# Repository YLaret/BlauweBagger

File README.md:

# BlauweBagger
This is the repository for the software that controls the Blauwe Bagger prototype installation.

## User Guide
After booting up the Raspberry Pi and going to the main page: [Main](http://192.168.0.100). The schematic overview should be visible (meters are being updated live, so can have different values):

The system always boots with all switches off (STOP mode).
### Automatic Control
To let the machine run on autopilot simply press `AUTO`. The machine will determine based on the sensors which pumps and motors to turn on/off.

### Manual Control
To control the switches manually, press `PAUSE` all the switches will turn off. Pressing on a pump or motor will turn it on/off. **Be careful: NO METER CONTROL, dangerous situation can occur.** 

### Timer Control (deprecated)
To run a timer based program, create stages with SwitchIDS and stageTimes and add these to a program. In the control view the program can be selected and executed. **NOTE:** the first program `Clay Unload` is a special program used by automatic control for the unload sequence, change with caution.

## Architecture
The controller is a Raspberry Pi module which controls the pumps and motors with Tuya enabled switches. The Pi will control the machine with a python service `machine.py`. This service will read the preferred state and write the actual state of the machine from and to a SQL database. A second service `server.py` hosts a local website that reads and writes the database values, allowing the user to control the machine remotely.
* `machine.py` will rely on the [gpiod](https://pypi.org/project/gpiod/) library for interaction with switches (GPIO)
* `server.py` will be based around Flask and nginx

### Database Architecture
The database follows a relational model with the following layout:

**NOTE1:** Upon upgrading the Tuya switches with SSR controlled by the GPIO, the **SWITCH** table does NOT contain: {MeterIDS, MeterMIN, MeterMax, IPAdress, LocalKey} anymore, instead: {SwitchID, Name, GPIO}.
**NOTE2:** A new table linking meters to switches called **METERRULES** containing:{MeterRuleID, MeterID, MeterThreshold, MeterThresholdGEQ, SwitchID, SwitchBool, Stage}.
## General Design Requirements
* ✅ Controlling pumps (manual, timed and automatic (senorbased)) using WebUI
* ✅ Flowmeter visualization in WebUI
* ✅ Pump control based on pressuresensor
* ✅ Log pump data (flow and power)
* ✅ Log and display errors and stalls
* ✅ Be transferable to new systems

### Webserver Design Requirements
* ✅ Schematic and tableview
* ✅ Way to create programs and controll machine manually
* ✅ Tableview with meters table, motors table and log window
* ✅ Schematicview with visualization of the plant (motor and flow meter states) and a log window
* ✅ Program view with timing possibilities

## Installation
### Installing Rasbian
* Download [Raspberry Pi OS Lite (64-bit)](https://www.raspberrypi.com/software/operating-systems/)
* Use Rasbian Imager to etch OS on an SD card
* Turn on SSH and add user `pi` with password [...]
* SSH into the Pi:
`ssh pi@[ipaddress]`
* Install pip, git and nginx:
```
sudo apt update
sudo apt upgrade
sudo apt install pip
sudo apt install git
sudo apt install nginx
```

Make sure python and pip are installed
* Clone the repository 
`git clone https://github.com/YLaret/BlauweBagger`
* Go to the BlauweBagger directory 
`cd BlauweBagger`
* Install the python dependencies 
`sudo pip install -r requirements.txt --break-system-packages`

## Running the webserver (for quick dev)
To run the webserver in developer modus:
```
cd server
export FLASK_APP=server
flask run --host=0.0.0.0
```
* After making some changes to the `server.py`, the server can be stopped by Ctr+C and restarted by the previous command

## Installing the webserver (permanent usage)
* Create a service for the server:
`sudo nano /etc/systemd/system/BlauweBagger.service`
* Copy paste the following:

```
[Unit]
Description=uWSGI instance to serve BlauweBagger server
After=network.target

[Service]
User=pi
Group=www-data
WorkingDirectory=/home/pi/BlauweBagger/server
ExecStart=/usr/local/bin/uwsgi --ini server.ini

[Install]
WantedBy=multi-user.target
```
* Enable the service:
```
sudo systemctl start BlauweBagger
sudo systemctl enable BlauweBagger
```

* Create start up script to fix permissions:
`sudo nano /etc/systemd/system/FixSocketPermissions.service`
* Copy and past the following:
```
[Unit]
Description=Fix socket permissions
After=network.target BlauweBagger.service

[Service]
ExecStart=/bin/bash -c "sudo chown pi:www-data /home/pi/BlauweBagger/server/server.sock; sudo chmod 660 /home/pi/BlauweBagger/server/server.sock; sudo chmod 755 /home/pi"
Type=oneshot
RemainAfterExit=yes

[Install]
WantedBy=multi-user.target
```
* Activate script:
```
sudo systemctl daemon-reload
sudo systemctl enable FixSocketPermissions
sudo systemctl start FixSocketPermissions
```

* Configure Nginx to proxy Request:
`sudo nano /etc/nginx/sites-available/BlauweBagger`
* Copy paste the following:

```
server {
    listen 80;
    server_name _;
location / {
        include uwsgi_params;
        uwsgi_pass unix:/home/pi/BlauweBagger/server/server.sock;
    }
}
```
* Link to enabled sites:
`sudo ln -s /etc/nginx/sites-available/BlauweBagger /etc/nginx/sites-enabled`
* Restart Nginx:
`sudo systemctl restart nginx`

## Running the machine program (for quick dev)
To run the machine program in developer modus:
```
cd machine
python machine.py
```

Exit the program with Ctr+C

## Installing the machine program (permanent usage)
* Create the service `sudo nano /etc/systemd/system/BlauweBaggerMachine.service`
* Copy and past the following:
```
[Unit]
Description=Python script controlling the machine
After=network.target

[Service]
User=pi
WorkingDirectory=/home/pi/BlauweBagger/machine
ExecStart=/usr/bin/python /home/pi/BlauweBagger/machine/machine.py
Restart=on-abort

[Install]
WantedBy=multi-user.target
```
* Start the script
```
sudo systemctl daemon-reload
sudo systemctl start BlauweBaggerMachine
sudo systemctl enable BlauweBaggerMachine
```

## Running the control program (for quick dev)
To run the control program in developer modus:
```
cd control
python control.py
```

Exit the program with Ctr+C

## Installing the machine program (permanent usage)
* Create the service `sudo nano /etc/systemd/system/BlauweBaggerControl.service`
* Copy and past the following:
```
[Unit]
Description=Python script controlling the hydrocyclone
After=network.target

[Service]
User=pi
WorkingDirectory=/home/pi/BlauweBagger/control
ExecStart=/usr/bin/python /home/pi/BlauweBagger/control/control.py
Restart=on-abort

[Install]
WantedBy=multi-user.target
```
* Start the script
```
sudo systemctl daemon-reload
sudo systemctl start BlauweBaggerControl
sudo systemctl enable BlauweBaggerControl
```
## Hydrocyclone Control
The ACC page provides hydrocyclone control. The `Ref` entry of the `CONTROL` table in the `machine.db` Sqlite3 database is used to determine the set point, the `auto` entry is used to toggle sensor control (e.g. when a sensor fails possible to turn of automatic control of the VFD). The control service source code is `control/control.py`.

## Tailscale (remote access)
To access the installation remotely Tailscale is used to create a mesh VPN to which the Raspberry Pi and the control client are connected. To install follow the [instructions](https://pypi.org/project/gpiod/) to install on the Raspberry Pi, login with an account (e.g. `blueboxvpn@gmail.com`) and install on the control client side as well (iOS, macOS, Windows or Linux) and login with the same account. Go to the ip-address of the Raspberry Pi (visible on Tailscale dashboard). On the control client connect to the Tailscale VPN and

## 5G router setup (Zyxel NR5307)
Check the connected devices and note the MAC-address of the raspberrypi (e.g. 1c:cf:67:67:3c:d8). Go to Home Network->Static DHCP insert a configuration with the MAC-address and the preferred IP-address (e.g. 192.168.1.100). This will be url to which local (non-VPN) devices (e.g. iPad) can connect to the machine.

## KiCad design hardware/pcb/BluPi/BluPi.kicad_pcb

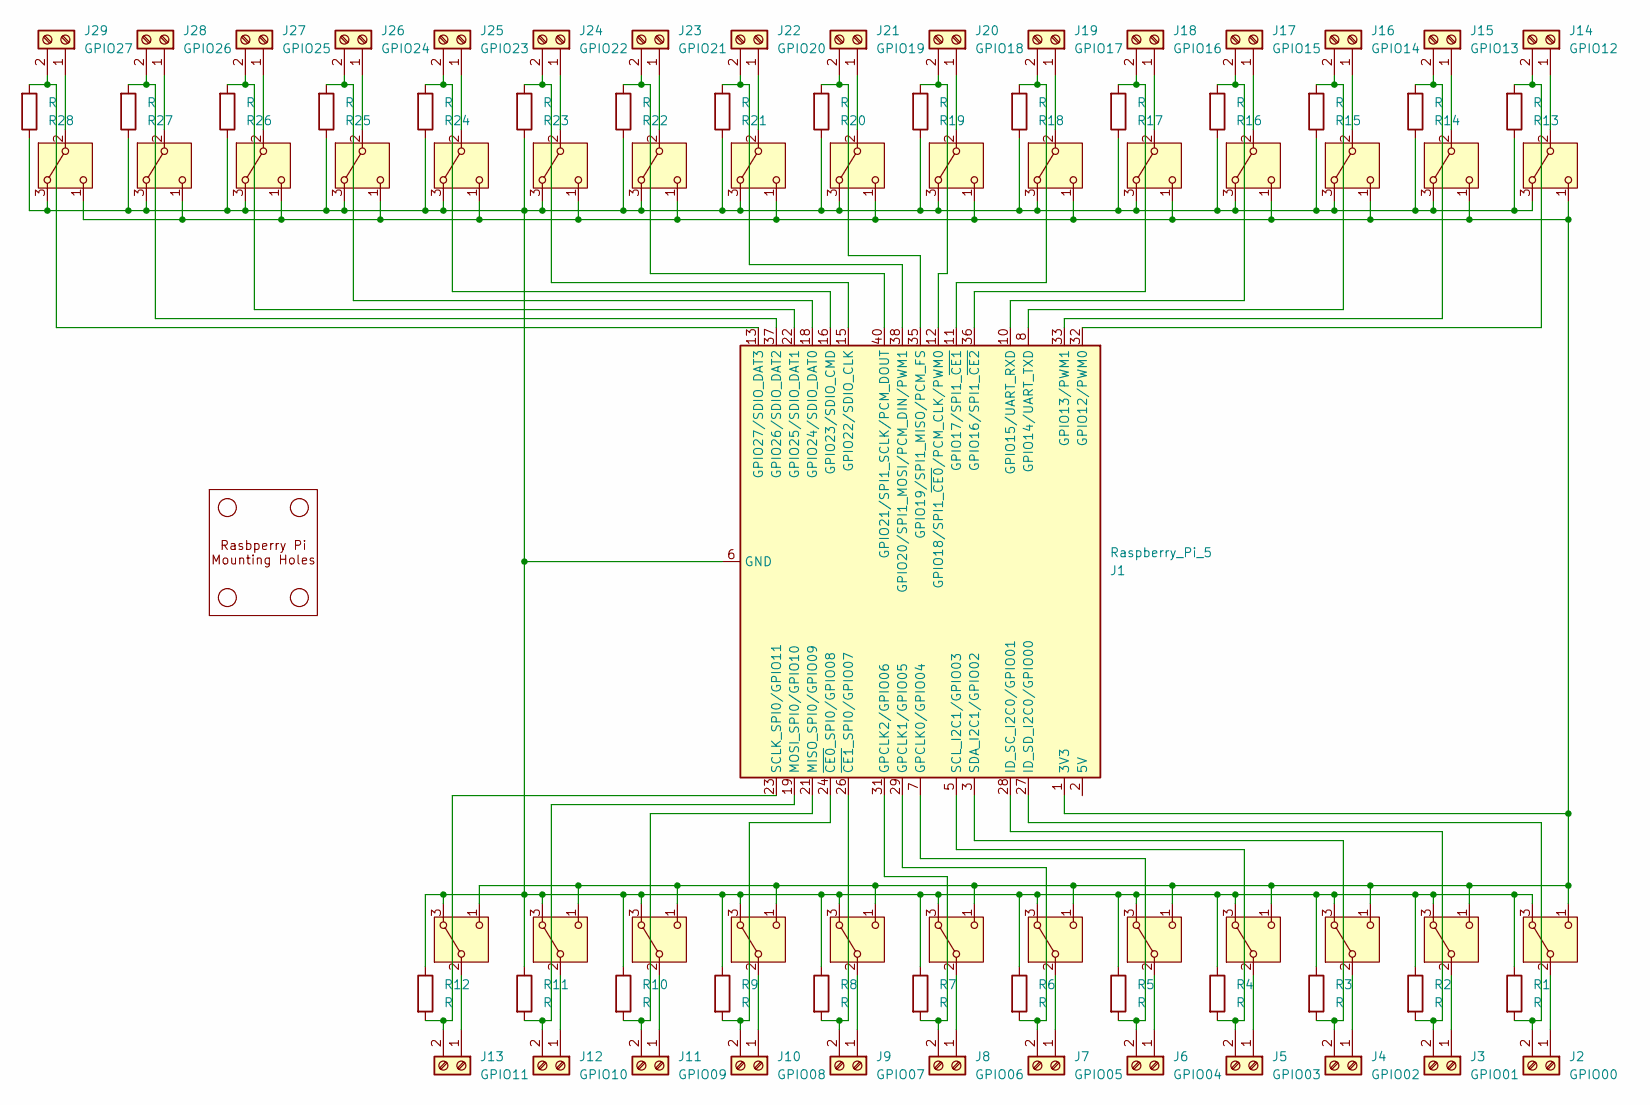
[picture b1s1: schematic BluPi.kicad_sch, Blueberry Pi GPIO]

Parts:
J1: Raspberry_Pi_5; PinHeader_2x20_P2.54mm_Vertical
J2: GPIO00; TerminalBlock_Phoenix_MKDS-1,5-2-5.08_1x02_P5.08mm_Horizont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
J3: GPIO01; TerminalBlock_Phoenix_MKDS-1,5-2-5.08_1x02_P5.08mm_Horizont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
J4: GPIO02; TerminalBlock_Phoenix_MKDS-1,5-2-5.08_1x02_P5.08mm_Horizont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
J5: GPIO03; TerminalBlock_Phoenix_MKDS-1,5-2-5.08_1x02_P5.08mm_Horizont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
J6: GPIO04; TerminalBlock_Phoenix_MKDS-1,5-2-5.08_1x02_P5.08mm_Horizont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
J7: GPIO05; TerminalBlock_Phoenix_MKDS-1,5-2-5.08_1x02_P5.08mm_Horizont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
J8: GPIO06; TerminalBlock_Phoenix_MKDS-1,5-2-5.08_1x02_P5.08mm_Horizont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
J9: GPIO07; TerminalBlock_Phoenix_MKDS-1,5-2-5.08_1x02_P5.08mm_Horizont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
J10: GPIO08; TerminalBlock_Phoenix_MKDS-1,5-2-5.08_1x02_P5.08mm_Horizont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
J11: GPIO09; TerminalBlock_Phoenix_MKDS-1,5-2-5.08_1x02_P5.08mm_Horizont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
J12: GPIO10; TerminalBlock_Phoenix_MKDS-1,5-2-5.08_1x02_P5.08mm_Horizont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
J13: GPIO11; TerminalBlock_Phoenix_MKDS-1,5-2-5.08_1x02_P5.08mm_Horizont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
J14: GPIO12; TerminalBlock_Phoenix_MKDS-1,5-2-5.08_1x02_P5.08mm_Horizont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
J15: GPIO13; TerminalBlock_Phoenix_MKDS-1,5-2-5.08_1x02_P5.08mm_Horizont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
J16: GPIO14; TerminalBlock_Phoenix_MKDS-1,5-2-5.08_1x02_P5.08mm_Horizont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
J17: GPIO15; TerminalBlock_Phoenix_MKDS-1,5-2-5.08_1x02_P5.08mm_Horizont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
J18: GPIO16; TerminalBlock_Phoenix_MKDS-1,5-2-5.08_1x02_P5.08mm_Horizont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
J19: GPIO17; TerminalBlock_Phoenix_MKDS-1,5-2-5.08_1x02_P5.08mm_Horizont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
J20: GPIO18; TerminalBlock_Phoenix_MKDS-1,5-2-5.08_1x02_P5.08mm_Horizont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
J21: GPIO19; TerminalBlock_Phoenix_MKDS-1,5-2-5.08_1x02_P5.08mm_Horizont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
J22: GPIO20; TerminalBlock_Phoenix_MKDS-1,5-2-5.08_1x02_P5.08mm_Horizont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
J23: GPIO21; TerminalBlock_Phoenix_MKDS-1,5-2-5.08_1x02_P5.08mm_Horizont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
J24: GPIO22; TerminalBlock_Phoenix_MKDS-1,5-2-5.08_1x02_P5.08mm_Horizont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
J25: GPIO23; TerminalBlock_Phoenix_MKDS-1,5-2-5.08_1x02_P5.08mm_Horizont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
J26: GPIO24; TerminalBlock_Phoenix_MKDS-1,5-2-5.08_1x02_P5.08mm_Horizont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
J27: GPIO25; TerminalBlock_Phoenix_MKDS-1,5-2-5.08_1x02_P5.08mm_Horizont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
J28: GPIO26; TerminalBlock_Phoenix_MKDS-1,5-2-5.08_1x02_P5.08mm_Horizont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
J29: GPIO27; TerminalBlock_Phoenix_MKDS-1,5-2-5.08_1x02_P5.08mm_Horizont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
R1, R2, R3, R4, R5, R6, R7, R8, R9, R10, R11, R12, R13, R14, R15, R16, R17, R18, R19, R20, R21, R22, R23, R24, R25, R26, R27, R28: R; R_0201_0603Metric_Pad0.64x0.40mm_HandSolder
SW1, SW2, SW3, SW4, SW5, SW6, SW7, SW8, SW9, SW10, SW11, SW12, SW13, SW14, SW15, SW16, SW17, SW18, SW19, SW20, SW21, SW22, SW23, SW24, SW25, SW26, SW27, SW28: SW_Nidec_CAS-120A1; Nidec_Copal_CAS-120A
U1: (no value)

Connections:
unnamed: J1.2 (5V), J1.4 (5V)
unnamed: J1.7 (GPCLK0/GPIO04), J6.2, R5.2
unnamed: J1.29 (GPCLK1/GPIO05), J7.2, R6.2
unnamed: J1.31 (GPCLK2/GPIO06), J8.2, R7.2
unnamed: J1.32 (GPIO12/PWM0), J14.2, R13.2
unnamed: J1.33 (GPIO13/PWM1), J15.2, R14.2
unnamed: J1.8 (GPIO14/UART_TXD), J16.2, R15.2
unnamed: J1.10 (GPIO15/UART_RXD), J17.2, R16.2
unnamed: J1.36 (GPIO16/SPI1_~CE2), J18.2, R17.2
unnamed: J1.11 (GPIO17/SPI1_~CE1), J19.2, R18.2
unnamed: J1.12 (GPIO18/SPI1_~CE0/PCM_CLK/PWM0), J20.2, R19.2
unnamed: J1.35 (GPIO19/SPI1_MISO/PCM_FS), J21.2, R20.2
unnamed: J1.38 (GPIO20/SPI1_MOSI/PCM_DIN/PWM1), J22.2, R21.2
unnamed: J1.40 (GPIO21/SPI1_SCLK/PCM_DOUT), J23.2, R22.2
unnamed: J1.15 (GPIO22/SDIO_CLK), J24.2, R23.2
unnamed: J1.16 (GPIO23/SDIO_CMD), J25.2, R24.2
unnamed: J1.18 (GPIO24/SDIO_DAT0), J26.2, R25.2
unnamed: J1.22 (GPIO25/SDIO_DAT1), J27.2, R26.2
unnamed: J1.37 (GPIO26/SDIO_DAT2), J28.2, R27.2
unnamed: J1.13 (GPIO27/SDIO_DAT3), J29.2, R28.2
unnamed: J1.28 (ID_SC_I2C0/GPIO01), J3.2, R2.2
unnamed: J1.27 (ID_SD_I2C0/GPIO00), J2.2, R1.2
unnamed: J1.21 (MISO_SPI0/GPIO09), J11.2, R10.2
unnamed: J1.19 (MOSI_SPI0/GPIO10), J12.2, R11.2
unnamed: J1.23 (SCLK_SPI0/GPIO11), J13.2, R12.2
unnamed: J1.5 (SCL_I2C1/GPIO03), J5.2, R4.2
unnamed: J1.3 (SDA_I2C1/GPIO02), J4.2, R3.2
unnamed: J1.24 (~CE0_SPI0/GPIO08), J10.2, R9.2
unnamed: J1.26 (~CE1_SPI0/GPIO07), J9.2, R8.2
unnamed: J2.1, SW1.2 (B)
unnamed: J3.1, SW2.2 (B)
unnamed: J4.1, SW3.2 (B)
unnamed: J5.1, SW4.2 (B)
unnamed: J6.1, SW5.2 (B)
unnamed: J7.1, SW6.2 (B)
unnamed: J8.1, SW7.2 (B)
unnamed: J9.1, SW8.2 (B)
unnamed: J10.1, SW9.2 (B)
unnamed: J11.1, SW10.2 (B)
unnamed: J12.1, SW11.2 (B)
unnamed: J13.1, SW12.2 (B)
unnamed: J14.1, SW13.2 (B)
unnamed: J15.1, SW14.2 (B)
unnamed: J16.1, SW15.2 (B)
unnamed: J17.1, SW16.2 (B)
unnamed: J18.1, SW17.2 (B)
unnamed: J19.1, SW18.2 (B)
unnamed: J20.1, SW19.2 (B)
unnamed: J21.1, SW20.2 (B)
unnamed: J22.1, SW21.2 (B)
unnamed: J23.1, SW22.2 (B)
unnamed: J24.1, SW23.2 (B)
unnamed: J25.1, SW24.2 (B)
unnamed: J26.1, SW25.2 (B)
unnamed: J27.1, SW26.2 (B)
unnamed: J28.1, SW27.2 (B)
unnamed: J29.1, SW28.2 (B)
unnamed: J1.6 (GND), J1.9 (GND), J1.14 (GND), J1.20 (GND), J1.25 (GND), J1.30 (GND), J1.34 (GND), J1.39 (GND), R1.1, R2.1, R3.1, R4.1, R5.1, R6.1, R7.1, R8.1, R9.1, R10.1, R11.1, R12.1, R13.1, R14.1, R15.1, R16.1, R17.1, R18.1, R19.1, R20.1, R21.1, R22.1, R23.1, R24.1, R25.1, R26.1, R27.1, R28.1, SW1.3 (A), SW2.3 (A), SW3.3 (A), SW4.3 (A), SW5.3 (A), SW6.3 (A), SW7.3 (A), SW8.3 (A), SW9.3 (A), SW10.3 (A), SW11.3 (A), SW12.3 (A), SW13.3 (A), SW14.3 (A), SW15.3 (A), SW16.3 (A), SW17.3 (A), SW18.3 (A), SW19.3 (A), SW20.3 (A), SW21.3 (A), SW22.3 (A), SW23.3 (A), SW24.3 (A), SW25.3 (A), SW26.3 (A), SW27.3 (A), SW28.3 (A)
unnamed: J1.1 (3V3), J1.17 (3V3), SW1.1 (C), SW2.1 (C), SW3.1 (C), SW4.1 (C), SW5.1 (C), SW6.1 (C), SW7.1 (C), SW8.1 (C), SW9.1 (C), SW10.1 (C), SW11.1 (C), SW12.1 (C), SW13.1 (C), SW14.1 (C), SW15.1 (C), SW16.1 (C), SW17.1 (C), SW18.1 (C), SW19.1 (C), SW20.1 (C), SW21.1 (C), SW22.1 (C), SW23.1 (C), SW24.1 (C), SW25.1 (C), SW26.1 (C), SW27.1 (C), SW28.1 (C)

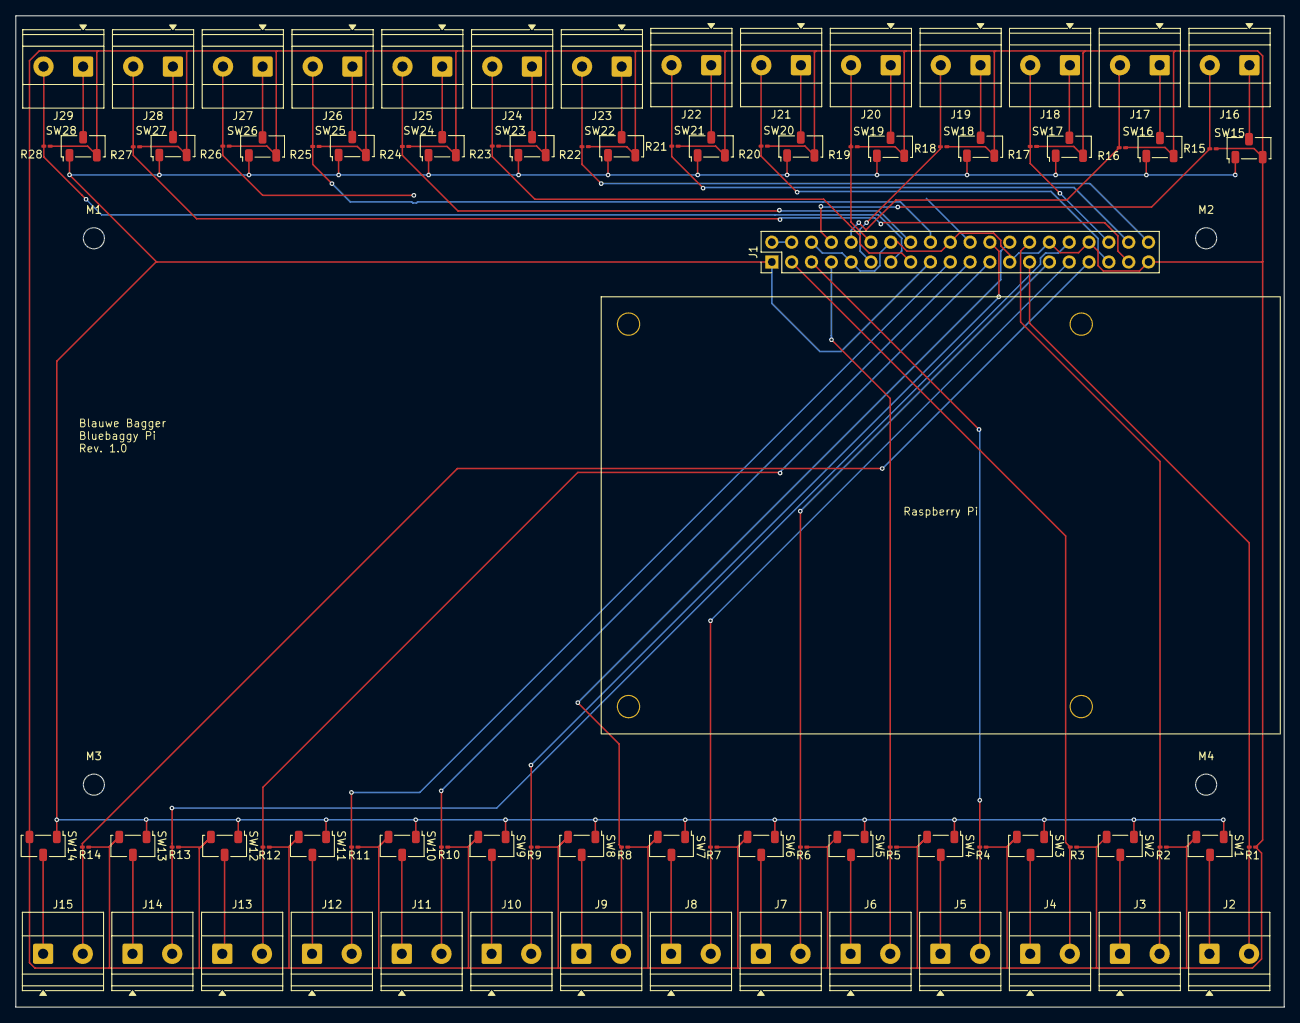
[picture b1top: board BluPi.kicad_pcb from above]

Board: 2 copper layers, 162.5 x 127.0 mm, 90 parts (0 on the bottom side), 59 nets.

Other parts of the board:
M1, M2, M3, M4: MountingHole_2.7mm
Raspberry Pi: Raspberry Pi 5 Mounting Holes; Raspberry_Pi_5_mounting_holes

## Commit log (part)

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2024-11-27 second commit
2024-11-27 third commit
2024-11-27 4 commit
2024-11-27 skirt
2024-11-27 wadabra
2024-11-27 clean sheet
2024-11-27 First sketch of the project
2024-11-27 small formatting fix
2024-12-02 added design requirements
2024-12-02 added transferability requirement
2024-12-02 added the main server start
2024-12-02 added requirements for webserver
2024-12-02 added an explantion of the database as well as the database architecture
2024-12-02 added the webserver developer running instructions
2024-12-02 added the machine outline
2024-12-02 added a first installation manual
2024-12-02 spelling fix
2024-12-02 added link to tinytuya
2024-12-02 updated the server instructions
2024-12-02 added sqlite3
2024-12-02 just a change of inventory
2024-12-02 first webserver outline framework
2024-12-02 inventory check
2024-12-02 first draft of webserver requirements
2024-12-02 formattting fix
2024-12-02 expanded requirements
2024-12-02 removed useless print statement
2024-12-03 increased automatic table generation
2024-12-03 implemented way to update database via the browser
2024-12-03 making the other table also updateable
2024-12-03 updated the column name to id in all tables
2024-12-03 added the tables to the program page, needs fix
2024-12-04 increased datatype compatability
2024-12-04 added a program table
2024-12-04 a start with the machine logic and program
2024-12-05 tuya library
2024-12-05 syntax error
2024-12-05 programState table
2024-12-05 improved automatic table generation
2024-12-05 a crude version of the machine executing programs
2024-12-05 updated explanation with new tables
2024-12-05 instructions for running the machine program
2024-12-05 formatting fix
2024-12-06 updated the description with the current state of the database
2024-12-07 proper closure of database connections in functions that access
2024-12-07 close database location fix
2024-12-07 fixed the close position really now
2024-12-07 syntax errors
2024-12-08 database diagram
2024-12-08 corrected link
2024-12-08 converted diagram to jpg
2024-12-09 localkey and old architecture
2024-12-09 EM1 and EM2 with localkey
2024-12-09 enabled the switching commands
2024-12-09 removed EM1 from database (main switch)
2024-12-09 device id is cryptic not EM1
2024-12-09 functional switches
2024-12-09 print statement more solid
2024-12-09 last tuya secret and modbus
2025-03-10 database architecture update
2025-03-10 readme with new archi
2025-03-10 readme with new archi (typo fix)
2025-03-10 readme with new archi (typo fix 2)
2025-03-11 database update and machine update
2025-03-11 added possibility to add rows and changed method modify rows
2025-03-11 half way backup commit (XCode is becoming unstable...)
2025-03-11 another backup push
2025-03-12 added flowsensor reading
2025-03-12 machine updates database with meter readings
2025-03-12 early phase auto update page
2025-03-12 typo fix
2025-03-12 another typo
2025-03-12 add jsonify lib
2025-03-12 typo
2025-03-12 log update
2025-03-12 check
2025-03-12 first attempt dynamic runtime
2025-03-12 dynamic meters, switches and runtime
2025-03-12 working dynamic homepage
2025-03-12 meter fix #1
2025-03-12 meter fix #2
2025-03-12 meter fix #3
2025-03-12 meter fix #4
2025-03-12 meter fix #5
2025-03-12 meter fix #6
2025-03-12 meter fix #7
2025-03-12 meter fixed
2025-03-12 last commit before pi transit
2025-03-12 leave switch 0/1 on in shutdown
2025-03-12 updated connect switches
2025-03-12 connect switch update
2025-03-12 removed switch 0 (idk where this one is, but it slows down the loop
2025-03-12 hopefully fixed speed problem
2025-03-12 speed attempt #1
2025-03-12 speed attempt #2
2025-03-19 database does not include critical switches
2025-03-19 removed wifi from readme
2025-03-19 added how to ssh into the pi
2025-03-19 added one program
2025-03-19 nowait var is the new speed up
2025-03-19 changed timing
2025-03-19 updated readme for installing permanent server
2025-03-19 readme typo
2025-03-19 added uwsgi req
2025-03-19 ini files
2025-03-19 time library
2025-03-19 changed turn off tuya
2025-03-19 better dsp for tuya 3.4
2025-03-19 machine install instructions
2025-03-19 fix with the nginx permissions
2025-03-20 added iPad 2 for dynamically updated webpages
2025-03-26 add a separate interval for the switches, async from the normal loop
2025-03-26 clarify the machine part of the read me
2025-03-30 more data on overview page
2025-03-30 forgot to return result
2025-03-30 now ther should be result
2025-03-31 resolved problem if no value
2025-03-31 first stage of overview remodelling
2025-03-31 java typo
2025-03-31 another java typo
2025-03-31 fixed stage out of bounds
2025-03-31 python syntax fix
2025-03-31 python logic fix
2025-03-31 indexing fix
2025-03-31 meter container and dynamic updates
2025-03-31 meter styling
2025-03-31 overview html architecture update
2025-03-31 forgotten class
2025-03-31 another forgotten class
2025-03-31 program info style update
2025-03-31 overview control architecture change
2025-03-31 final styling of overview
2025-03-31 active switch class fix
2025-03-31 ipad 2 button fix attempt #1
2025-03-31 ipad 2 button fix attempt #2
2025-03-31 some more old ipad fixes
2025-03-31 some more old ipad fixes #2
2025-03-31 last styling details
2025-03-31 last styling details for ipad 2
2025-03-31 limited the decimals on time and meters
2025-03-31 typo in overview app route
2025-03-31 first step progress bar
2025-03-31 proper progress bar integration
2025-04-01 todo list and some clean up
2025-04-01 more clean up
2025-04-02 add next and previous buttons
2025-04-02 typo server
2025-04-02 proper next stage time
2025-04-02 better icon next and prev buttons
2025-04-12 force the swtiches outside interval #1
2025-04-12 force function success
2025-04-12 logging functionality
2025-04-12 forgotten library
2025-04-13 log added to navbar no more table view
2025-04-13 exception for FORCE table
2025-04-13 right boolean
2025-04-13 improved table order => stage and program on top
2025-09-19 gpio req, for switch control
2025-09-19 database arch update for gpio
2025-09-19 gpio machine arch, rudimental meter control
2025-09-29 force stop on start up implemented
2025-09-29 auto button server side
2025-09-29 error fix, auto button working on server side
2025-11-04 1st it auto program
2025-11-04 database rule correction, init auto with no activeSw
2025-11-05 doseer pomp auto
2025-11-05 wrap the multitude of switches
2025-11-05 unload sequence auto
2025-11-05 gpio update
2025-11-05 gpio pinout fix
2025-11-05 fixed gpio active init
2025-11-05 missing rule for doseer
2025-11-05 fixed switchid doseer
2025-11-05 HMI working, no meters
2025-11-06 live meters in hmi
2025-11-06 meter unit removed
2025-11-06 hmi -> homepage, navbar update
2025-11-06 add manual
2025-11-06 link fix
2025-11-06 rearrange user guide
2025-11-06 timer program clarification
2025-11-06 allignment fix
2025-11-06 base file for schematic overview
2026-02-06 pers druk + suspend to unload
2026-03-24 GPIO changes and server install improvement
2026-06-14 agrat surogate
2026-06-14 agrat
2026-06-14 agrate
